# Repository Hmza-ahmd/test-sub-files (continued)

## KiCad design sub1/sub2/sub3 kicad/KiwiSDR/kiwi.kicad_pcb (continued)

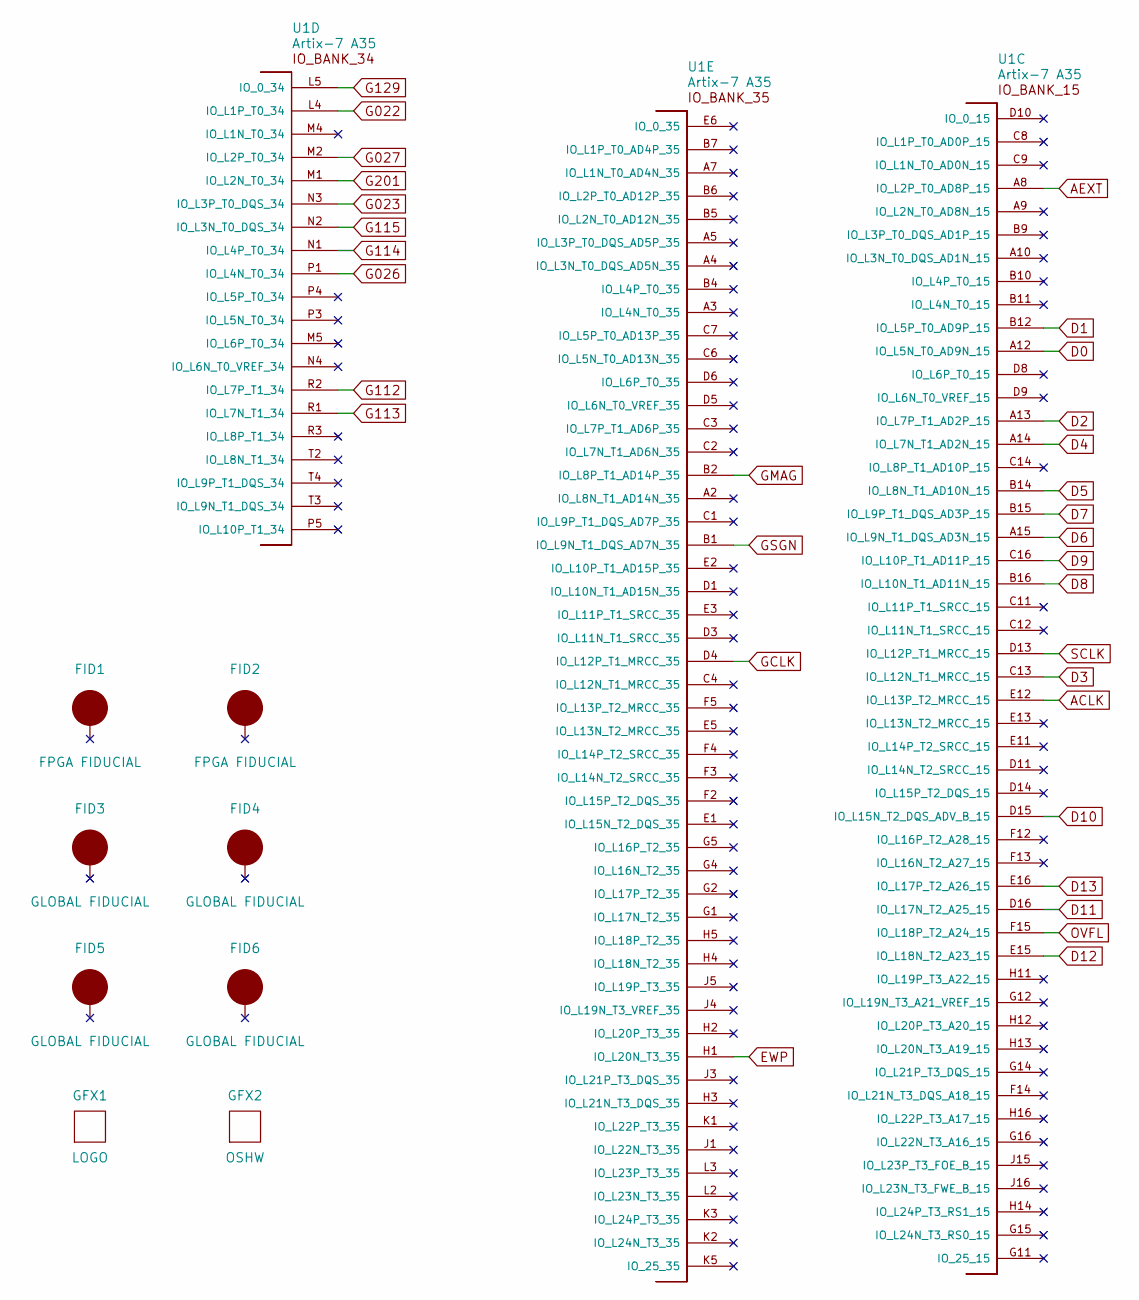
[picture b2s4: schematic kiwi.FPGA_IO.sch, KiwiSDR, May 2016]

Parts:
FID1, FID2: FPGA FIDUCIAL; kiwi-FIDUCIAL
FID3, FID4, FID5, FID6: GLOBAL FIDUCIAL; kiwi-FIDUCIAL
GFX1: LOGO; kiwi-KIWI_10MM
GFX2: OSHW; kiwi-OSHW_6MM
U1: Artix-7 A35; kiwi-FTG256

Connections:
ACLK: U1.E12 (IO_L13P_T2_MRCC_15); also elsewhere on the board
AEXT: U1.A8 (IO_L2P_T0_AD8P_15); also elsewhere on the board
D0: U1.A12 (IO_L5N_T0_AD9N_15); also elsewhere on the board
D1: U1.B12 (IO_L5P_T0_AD9P_15); also elsewhere on the board
D2: U1.A13 (IO_L7P_T1_AD2P_15); also elsewhere on the board
D3: U1.C13 (IO_L12N_T1_MRCC_15); also elsewhere on the board
D4: U1.A14 (IO_L7N_T1_AD2N_15); also elsewhere on the board
D5: U1.B14 (IO_L8N_T1_AD10N_15); also elsewhere on the board
D6: U1.A15 (IO_L9N_T1_DQS_AD3N_15); also elsewhere on the board
D7: U1.B15 (IO_L9P_T1_DQS_AD3P_15); also elsewhere on the board
D8: U1.B16 (IO_L10N_T1_AD11N_15); also elsewhere on the board
D9: U1.C16 (IO_L10P_T1_AD11P_15); also elsewhere on the board
D10: U1.D15 (IO_L15N_T2_DQS_ADV_B_15); also elsewhere on the board
D11: U1.D16 (IO_L17N_T2_A25_15); also elsewhere on the board
D12: U1.E15 (IO_L18N_T2_A23_15); also elsewhere on the board
D13: U1.E16 (IO_L17P_T2_A26_15); also elsewhere on the board
EWP: U1.H1 (IO_L20N_T3_35); also elsewhere on the board
G022: U1.L4 (IO_L1P_T0_34); also elsewhere on the board
G023: U1.N3 (IO_L3P_T0_DQS_34); also elsewhere on the board
G026: U1.P1 (IO_L4N_T0_34); also elsewhere on the board
G027: U1.M2 (IO_L2P_T0_34); also elsewhere on the board
G112: U1.R2 (IO_L7P_T1_34); also elsewhere on the board
G113: U1.R1 (IO_L7N_T1_34); also elsewhere on the board
G114: U1.N1 (IO_L4P_T0_34); also elsewhere on the board
G115: U1.N2 (IO_L3N_T0_DQS_34); also elsewhere on the board
G129: U1.L5 (IO_0_34); also elsewhere on the board
G201: U1.M1 (IO_L2N_T0_34); also elsewhere on the board
GCLK: U1.D4 (IO_L12P_T1_MRCC_35); also elsewhere on the board
GMAG: U1.B2 (IO_L8P_T1_AD14P_35); also elsewhere on the board
GSGN: U1.B1 (IO_L9N_T1_DQS_AD7N_35); also elsewhere on the board
OVFL: U1.F15 (IO_L18P_T2_A24_15); also elsewhere on the board
SCLK: U1.D13 (IO_L12P_T1_MRCC_15); also elsewhere on the board

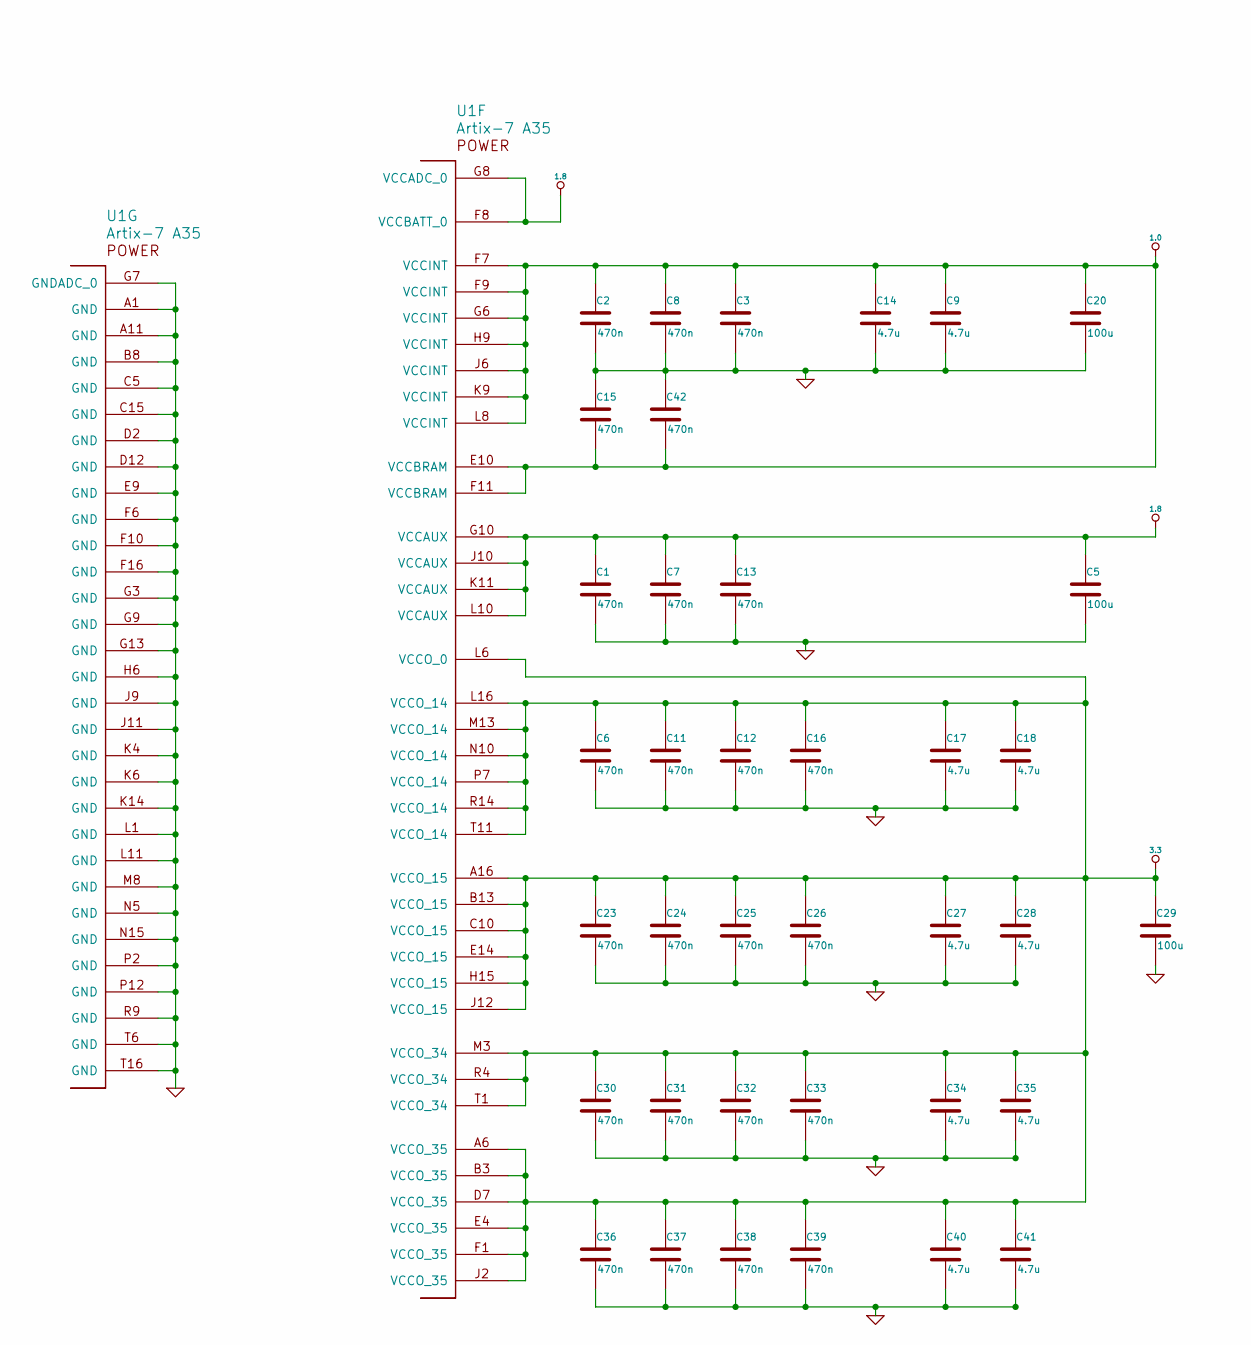
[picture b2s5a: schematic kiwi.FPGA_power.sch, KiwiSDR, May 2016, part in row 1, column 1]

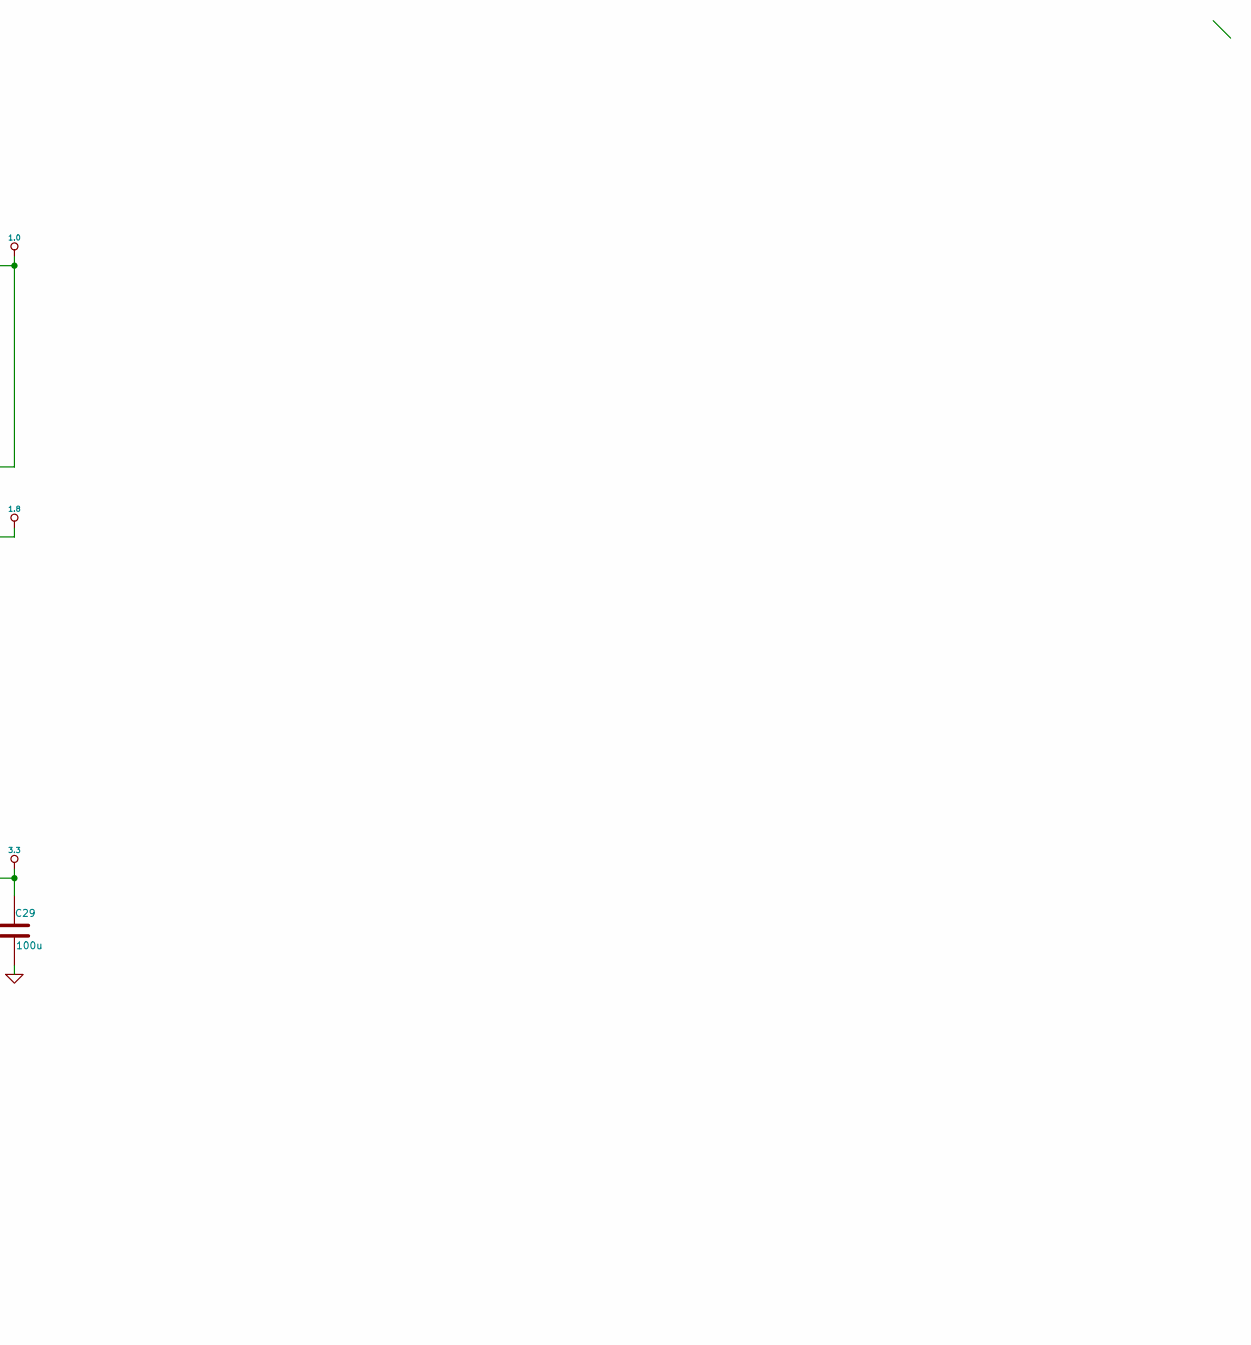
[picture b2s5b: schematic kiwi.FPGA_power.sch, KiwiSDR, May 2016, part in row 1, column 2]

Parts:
C1, C2, C3, C6, C7, C8, C11, C12, C13, C15, C16, C23, C24, C25, C26, C30, C31, C32, C33, C36, C37, C38, C39, C42: 470n; kiwi-SM0402
C5, C20, C29: 100u; kiwi-SM1206
C9, C14, C17, C18, C27, C28, C34, C35, C40, C41: 4.7u; kiwi-SM0402
U1: Artix-7 A35; kiwi-FTG256

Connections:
1.0: C2.1, C3.1, C8.1, C9.1, C14.1, C15.2, C20.1, C42.2, U1.E10 (VCCBRAM), U1.F7 (VCCINT), U1.F9 (VCCINT), U1.F11 (VCCBRAM), U1.G6 (VCCINT), U1.H9 (VCCINT), U1.J6 (VCCINT), U1.K9 (VCCINT), U1.L8 (VCCINT); also elsewhere on the board
1.8: C1.1, C5.1, C7.1, C13.1, U1.F8 (VCCBATT_0), U1.G8 (VCCADC_0), U1.G10 (VCCAUX), U1.J10 (VCCAUX), U1.K11 (VCCAUX), U1.L10 (VCCAUX); also elsewhere on the board

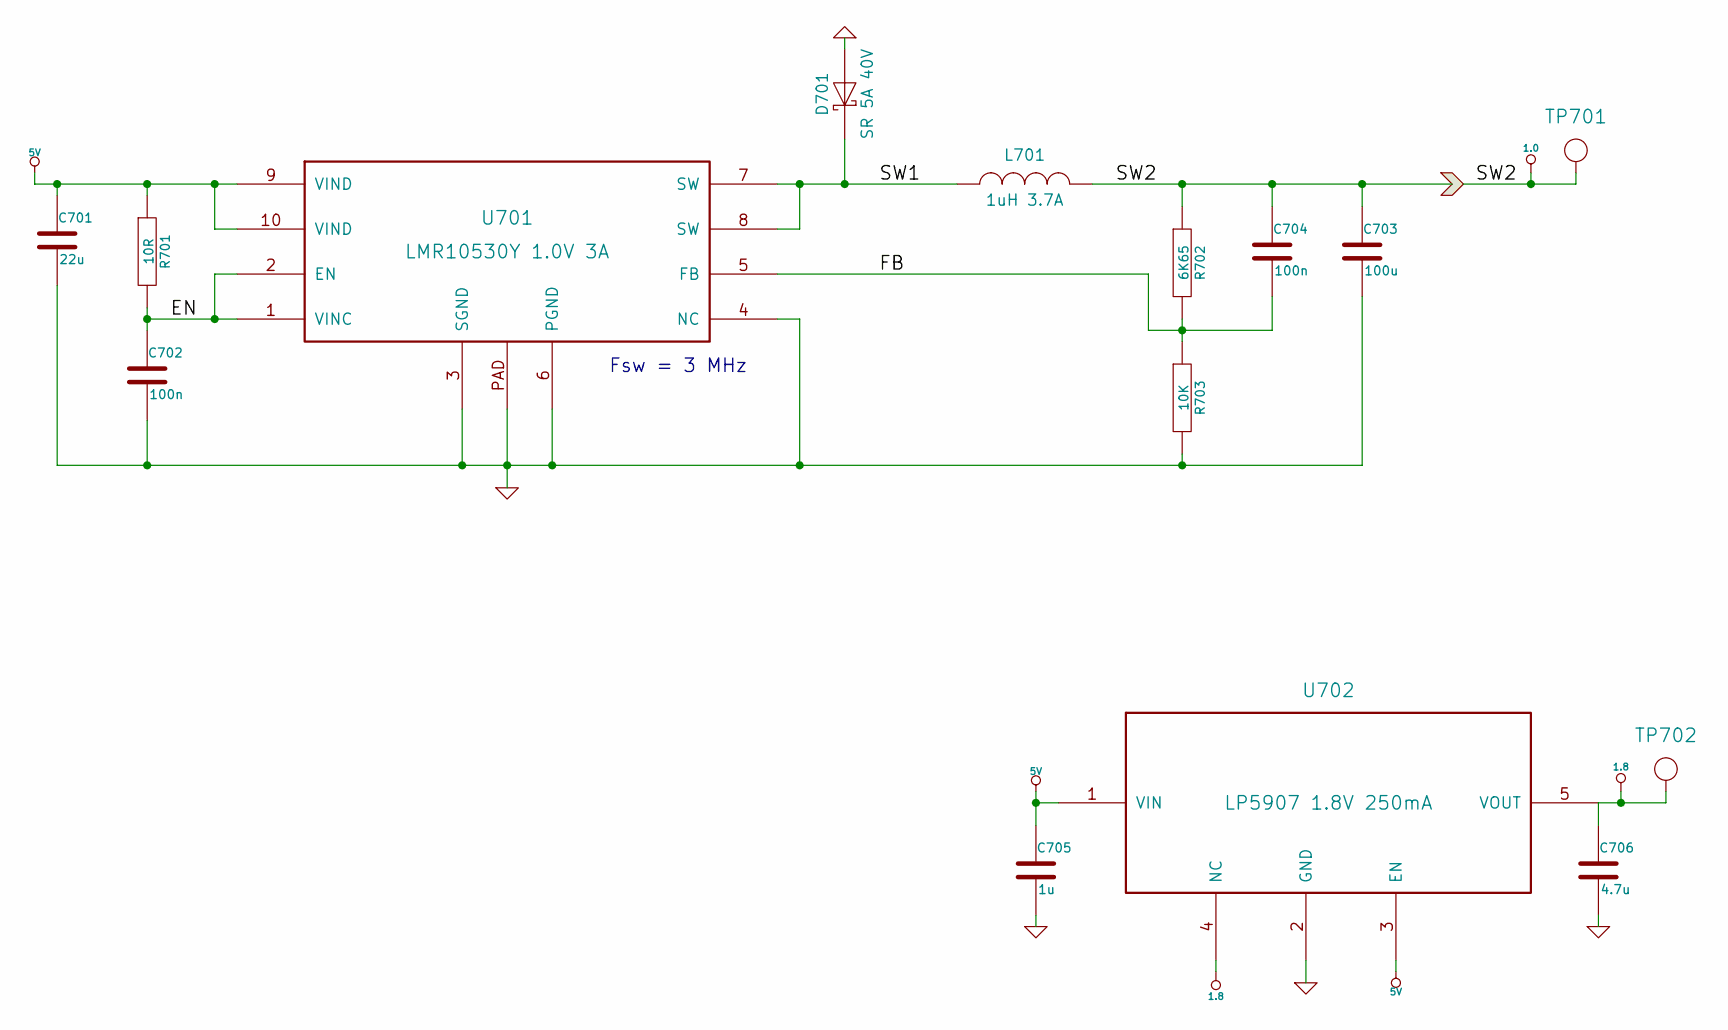
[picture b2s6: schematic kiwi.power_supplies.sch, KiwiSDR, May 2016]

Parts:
C701: 22u; kiwi-SM0805
C702, C704: 100n; kiwi-SM0402
C703: 100u; kiwi-SM1206
C705: 1u; kiwi-SM0402
C706: 4.7u; kiwi-SM0402
D701: SR 5A 40V; kiwi-DO214_AA
L701: 1uH 3.7A; kiwi-INDUCTOR_4x4
R701: 10R; kiwi-SM0402
R702: 6K65; kiwi-SM0402
R703: 10K; kiwi-SM0402
TP701, TP702: TEST_POINT; kiwi-TP_600
U701: LMR10530Y 1.0V 3A; kiwi-WSON10
U702: LP5907 1.8V 250mA; kiwi-SOT23_5

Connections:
1.0: C703.1, C704.1, L701.2, R702.1, TP701.1; also elsewhere on the board
1.8: C706.1, TP702.1, U702.4 (NC), U702.5 (VOUT); also elsewhere on the board
/Power_Supplies/EN: C702.1, R701.2, U701.1 (VINC), U701.2 (EN)
/Power_Supplies/FB: C704.2, R702.2, R703.1, U701.5 (FB)
/Power_Supplies/SW1: D701.1 (K), L701.1, U701.7 (SW), U701.8 (SW)

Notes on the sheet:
Fsw = 3 MHz

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
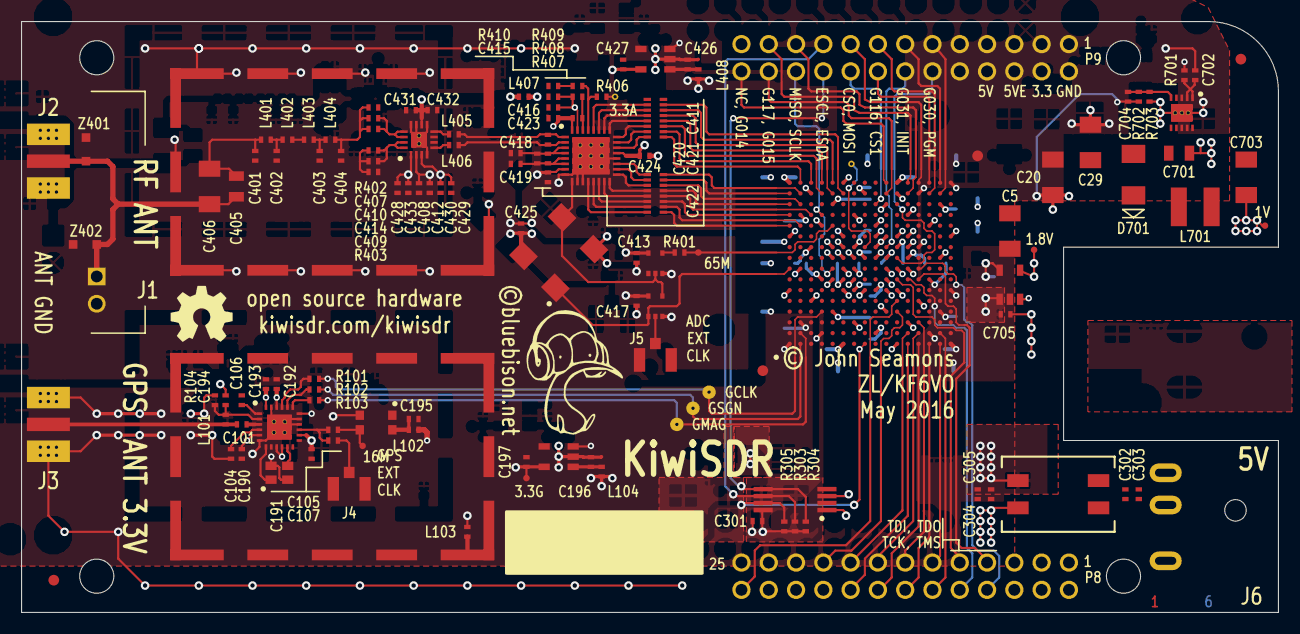
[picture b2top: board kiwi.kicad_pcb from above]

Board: 6 copper layers, 117.0 x 55.0 mm, 174 parts (0 on the bottom side), 119 nets.

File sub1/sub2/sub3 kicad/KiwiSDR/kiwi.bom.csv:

#1, 1, 0R, Panasonic, ERJ-2GE0R00X, kiwi-SM0402, R408
#2, 1, 10R, Panasonic, ERJ-2RKF10R0X, kiwi-SM0402, R701
#3, 1, 28R7, Panasonic, ERJ-2RKF28R7X, kiwi-SM0402, R403
#4, 1, 66R5, Panasonic, ERJ-2RKF66R5X, kiwi-SM0402, R402
#5, 4, 100R, Panasonic, ERJ-2RKF1000X, kiwi-SM0402, R101 R102 R103 R401
#6, 1, 1K5, Panasonic, ERJ-2RKF1501X, kiwi-SM0402, R104
#7, 3, 5K6, Panasonic, ERJ-2RKF5601X, kiwi-SM0402, R303 R304 R305
#8, 1, 6K65, Panasonic, ERJ-2RKF6651X, kiwi-SM0402, R702
#9, 4, 10K, Panasonic, ERJ-2RKF1002X, kiwi-SM0402, R406 R409 R410 R703
#10, 2, 100R, Bourns, CAY16-101J8LF, kiwi-RNET_CAY16_J8, R404 R405
#11, 2, 22p, Murata, GRM1555C1H220JA01D, kiwi-SM0402, C101 C104
#12, 2, 56p/100, Murata, GRM1555C2A560JA01D, kiwi-SM0402, C401 C404
#13, 4, 100p, Murata, GRM1555C1H101JA01D, kiwi-SM0402, C194 C408 C411 C416
#14, 2, 160p/50, Murata, GRM1555C1H161JA01D, kiwi-SM0402, C402 C403
#15, 5, 1n, Murata, GCM155R71H102KA37D, kiwi-SM0402, C407 C409 C428 C430 C432
#16, 8, 10n, Murata, GRM155R71C103KA01D, kiwi-SM0402, C105 C106 C193 C303 C305 C413 C417 C425
#17, 14, 100n, Murata, GRM155R71C104KA88D, kiwi-SM0402, C190 C191 C192 C195 C301 C421 C422 C423 C424 C429 C431 C433 C702 C704
#18, 28, 470n, Murata, GRM155R6YA474KE01D, kiwi-SM0402, C1 C2 C3 C6 C7 C8 C11 C12 C13 C15 C16 C23 C24 C25 C26 C30 C31 C32 C33 C36 C37 C38 C39 C42 C302 C304 C410 C414
#19, 7, 1u, Murata, GRM155R61E105KA12D, kiwi-SM0402, C196 C197 C418 C419 C426 C427 C705
#20, 3, 2.2u, Murata, GRM155R60J225ME15D, kiwi-SM0402, C412 C415 C420
#21, 11, 4.7u, Murata, GRM155R60J475ME47D, kiwi-SM0402, C9 C14 C17 C18 C27 C28 C34 C35 C40 C41 C706
#22, 1, 1n/100, Murata, GRM219R72A102KA01J, kiwi-SM0805, C405
#23, 1, 22u, Murata, GRM21BR60J226ME39L, kiwi-SM0805, C701
#24, 1, 470n/100, AVX, ESD61C474K4T2A-28, kiwi-SM1206, C406
#25, 4, 100u, Murata, GRM31CR60J107ME39L, kiwi-SM1206, C5 C20 C29 C703
#26, 5, FB 600Z, TDK, MMZ1005B601C, kiwi-SM0402, L102 L103 L104 L407 L408
#27, 1, 39nH, TDK, MLK1005S39NJ, kiwi-SM0402, L101
#28, 3, 150nH, TDK, MLG1005SR15J, kiwi-SM0402, L403 L405 L406
#29, 1, 270nH, TDK, MLG1005SR27J, kiwi-SM0402, L402
#30, 2, 330nH, TDK, MLG1005SR33J, kiwi-SM0402, L401 L404
#31, 1, 1uH 3.7A, Bourns, SRN4018-1R0Y, kiwi-INDUCTOR_4x4, L701
#32, 1, CMC 500uH 1A, Bourns, SRF0905A-501Y, kiwi-CMC, T301
#33, 1, SAW L1, RFM, SF1186G, kiwi-SAW, FL101
#34, 1, SE4150L, Skyworks, SE4150L-R, kiwi-QFN24, U101
#35, 1, EEPROM 32Kx8, On Semi, CAT24C256YI-GT3, kiwi-TSSOP8, U301
#36, 2, NC7SZ125, Fairchild, NC7SZ125P5X, kiwi-SC70_5, U403 U406
#37, 1, LMR10530Y 1.0V 3A, TI, LMR10530YSD/NOPB, kiwi-WSON10, U701
#38, 2, LP5907 3.3V 250mA, TI, LP5907QMFX-3.3Q1, kiwi-SOT23_5, U104 U404
#39, 1, LP5907 1.8V 250mA, TI, LP5907QMFX-1.8Q1, kiwi-SOT23_5, U702
#40, 1, SR 5A 40V, Vishay, SSB44-E3/52T, kiwi-DO214_AA, D701
#41, 2, TVS 3.3V, Bourns, CDSOD323-T03C, kiwi-SOD323, Z401 Z402
#42, 1, 66.6666 MHz, Conner Winfield, CWX823-066.6666M, kiwi-XO, U402
#43, 1, 16.368 MHz, TXC, 7Q-16.368MBG-T, kiwi-TCXO, X101
#44, 2, RF_SHIELD 29x19, Laird, BMI-S-209-F, *, ZR401 ZR101
#45, 2, RF_SHIELD_COVER 29x19, Laird, BMI-S-209-C, kiwi-RF_SHIELD_COVER, ZR102 ZR402
#46, 1, Artix-7 A35, Xilinx, XC7A35T-1FTG256C, kiwi-FTG256, U1
#47, 1, LTC2248, Linear Tech, LTC2248CUH#PBF, kiwi-QFN32, U401
#48, 1, LTC6401-20, Linear Tech, LTC6401CUD-20#PBF, kiwi-QFN16, U405

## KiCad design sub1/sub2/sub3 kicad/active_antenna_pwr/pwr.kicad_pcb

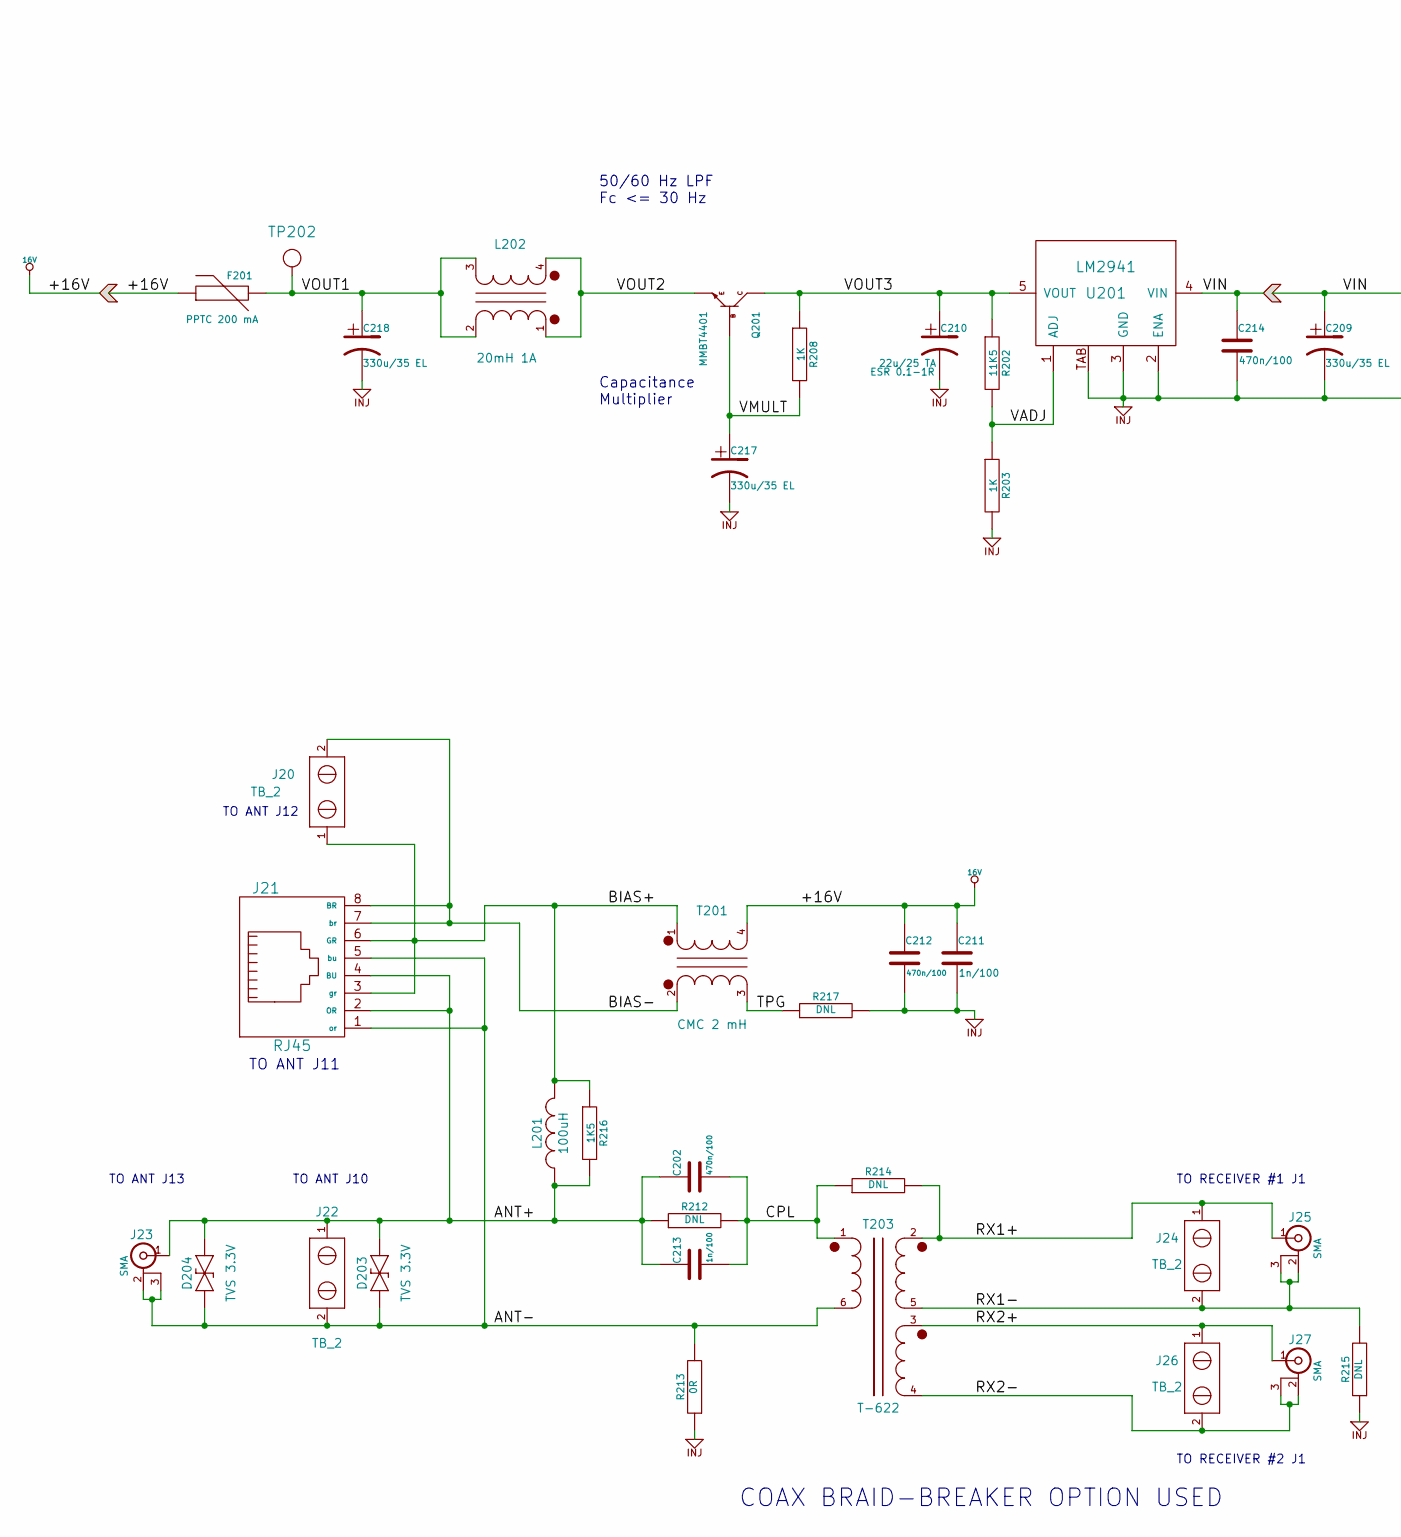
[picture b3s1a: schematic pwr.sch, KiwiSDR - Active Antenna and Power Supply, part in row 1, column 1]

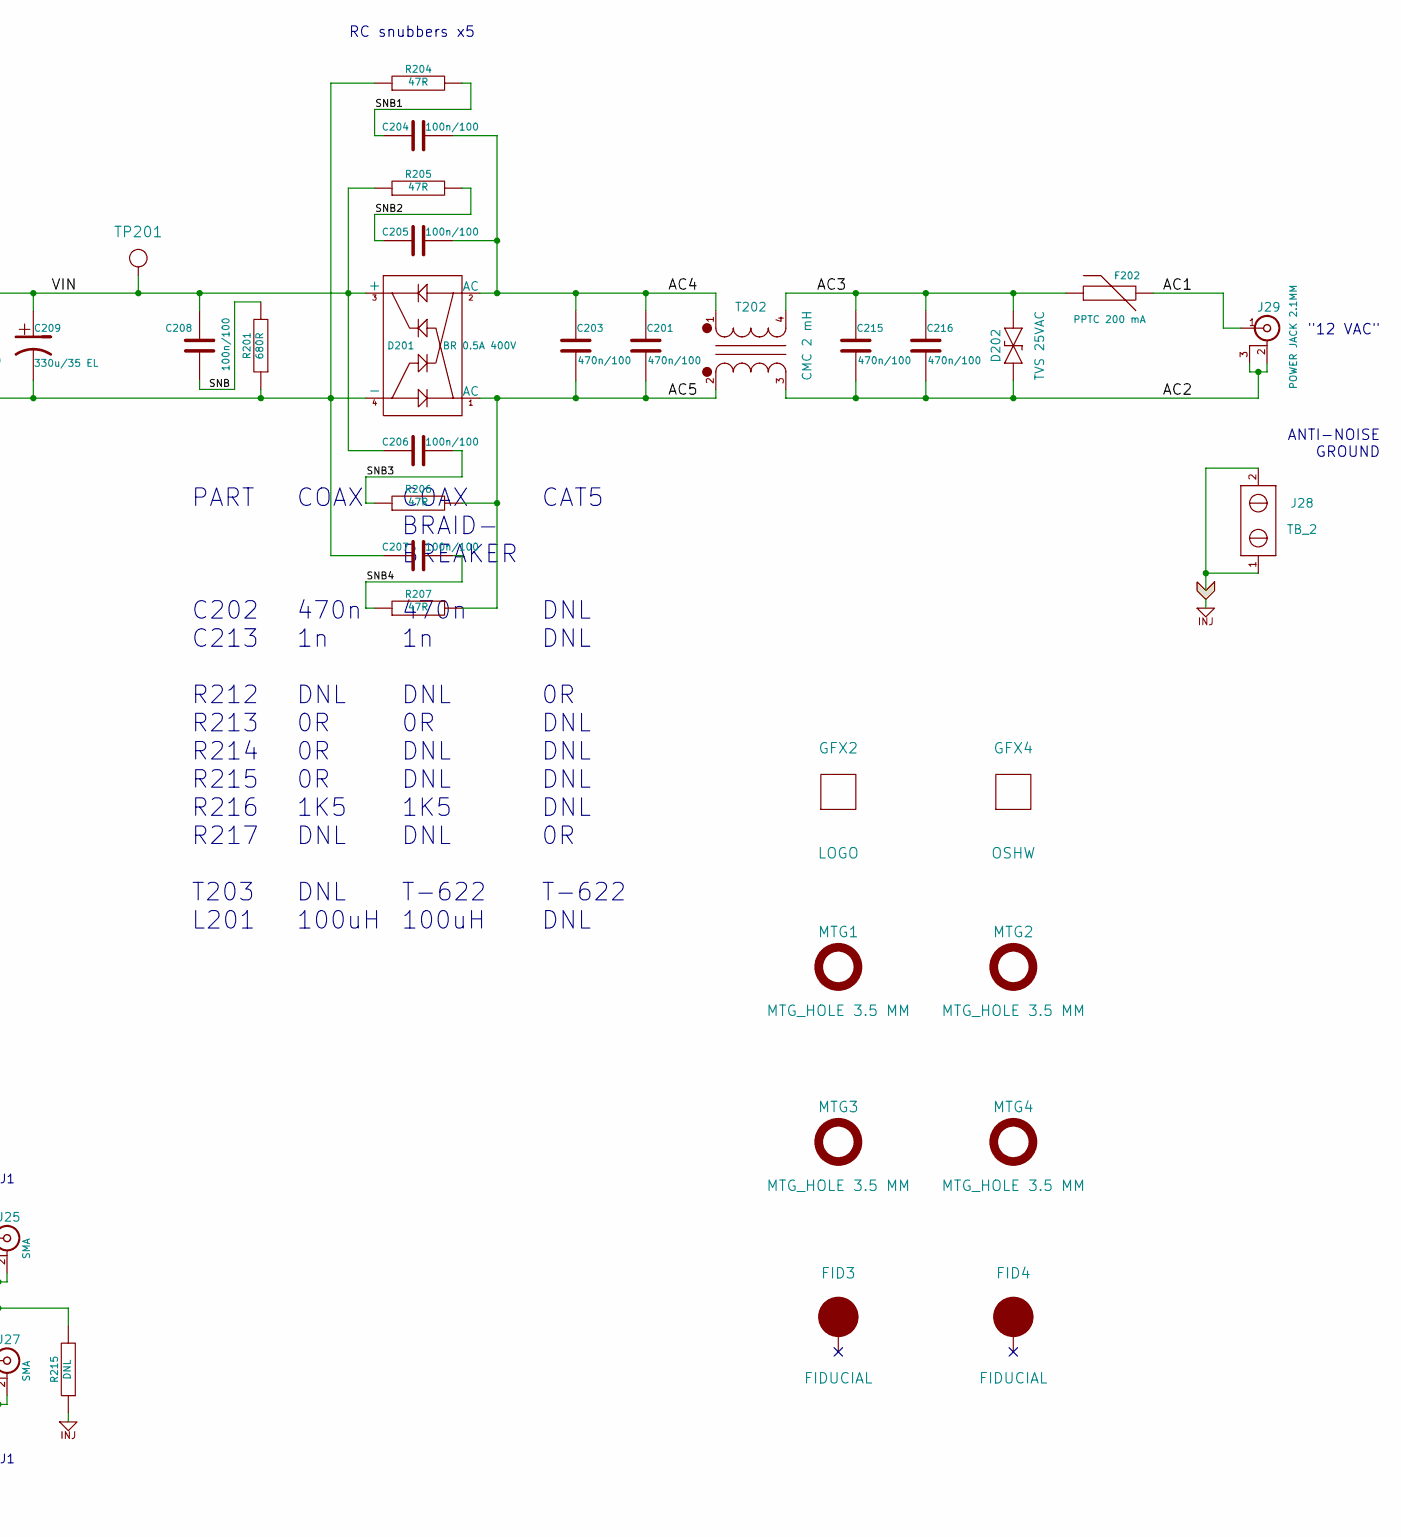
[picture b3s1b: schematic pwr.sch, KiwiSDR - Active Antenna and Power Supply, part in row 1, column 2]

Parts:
C201, C202, C203, C212, C214, C215, C216: 470n/100; kiwi-SM1206
C204, C205, C206, C207, C208: 100n/100; kiwi-SM0805
C209, C217, C218: 330u/35 EL; kiwi-CAP_10x10
C210: 22u/25 TA; kiwi-CAP_D
C211, C213: 1n/100; kiwi-SM0805
D201: BR 0.5A 400V; kiwi-TO269_AA
D202: TVS 25VAC; kiwi-SM0805
D203, D204: TVS 3.3V; kiwi-SOD323
F201, F202: PPTC 200 mA; kiwi-SM1812
FID3, FID4: FIDUCIAL; kiwi-FIDUCIAL
GFX2: LOGO; kiwi-KIWI_10MM
GFX4: OSHW; kiwi-OSHW_6MM
J20, J22, J24, J26, J28: TB_2; kiwi-TB_2P_2_54MM
J21: RJ45; kiwi-RJ45_8
J23, J25, J27: SMA; kiwi-BNC_SMA_NO_VIP
J29: POWER JACK 2.1MM; kiwi-DC_JACK_2_1MM
L201: 100uH; kiwi-SM1812
L202: 20mH 1A; kiwi-CMC_22x22
MTG1, MTG2, MTG3, MTG4: MTG_HOLE 3.5 MM; kiwi-MTG_NPTH_3_5MM
Q201: MMBT4401; kiwi-SOT23_BCE
R201: 680R; kiwi-SM0805
R202: 11K5; kiwi-SM0805
R203, R208: 1K; kiwi-SM0805
R204, R205, R206, R207: 47R; kiwi-SM0805
R212, R214, R215, R217: DNL; kiwi-SM0805
R213: 0R; kiwi-SM0805
R216: 1K5; kiwi-SM0805
T201, T202: CMC 2 mH; kiwi-CMC
T203: T-622; kiwi-MCL_KK81
TP201, TP202: TEST_POINT; kiwi-TP_1250
U201: LM2941; kiwi-TO263

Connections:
/AC1: F202.2, J29.1 (In)
/AC2: C215.2, C216.2, D202.1, J29.2 (gnd), J29.3 (gnd), T202.3
/AC3: C215.1, C216.1, D202.2, F202.1, T202.4
/AC4: C201.1, C203.1, C204.2, C205.2, D201.2 (AC), T202.1
/AC5: C201.2, C203.2, D201.1 (AC), R206.2, R207.2, T202.2
/ANT+: C202.1, C213.1, D203.2, D204.2, J21.2 (OR), J21.4 (BU), J22.1, J23.1 (In), L201.1, R212.1, R216.2
/ANT-: D203.1, D204.1, J21.1 (or), J21.5 (bu), J22.2, J23.2 (gnd), J23.3 (gnd), R213.2, T203.6
/BIAS+: J20.1, J21.3 (gr), J21.6 (GR), L201.2, R216.1, T201.1
/BIAS-: J20.2, J21.7 (br), J21.8 (BR), T201.2
/CPL: C202.2, C213.2, R212.2, R214.1, T203.1
/RX1+: J24.1, J25.1 (In), R214.2, T203.2
/RX1-: J24.2, J25.2 (gnd), J25.3 (gnd), R215.2, T203.5
/RX2+: J26.1, J27.1 (In), T203.3
/RX2-: J26.2, J27.2 (gnd), J27.3 (gnd), T203.4
/SNB: C208.2, R201.2
/SNB1: C204.1, R204.2
/SNB2: C205.1, R205.2
/SNB3: C206.2, R206.1
/SNB4: C207.2, R207.1
/TPG: R217.1, T201.3
/VADJ: R202.2, R203.1, U201.1 (ADJ)
/VMULT: C217.1, Q201.B, R208.2
/VOUT1: C218.1, F201.2, L202.2, L202.3, TP202.1
/VOUT2: L202.1, L202.4, Q201.E
/VOUT3: C210.1, Q201.C, R202.1, R208.1, U201.5 (VOUT)

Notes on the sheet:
"12 VAC"
RC snubbers x5
PART C202 C213 R212 R213 R214 R215 R216 R217 T203 L201
COAX BRAID- BREAKER 470n 1n DNL 0R DNL DNL 1K5 DNL T-622 100uH
CAT5 DNL DNL 0R DNL DNL DNL DNL 0R T-622 DNL
TO ANT J12
TO ANT J11
TO RECEIVER #1 J1
TO ANT J10
50/60 Hz LPF Fc <= 30 Hz
Capacitance Multiplier
ANTI-NOISE GROUND
COAX 470n 1n DNL 0R 0R 0R 1K5 DNL DNL 100uH
TO ANT J13
TO RECEIVER #2 J1
COAX BRAID-BREAKER OPTION USED

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
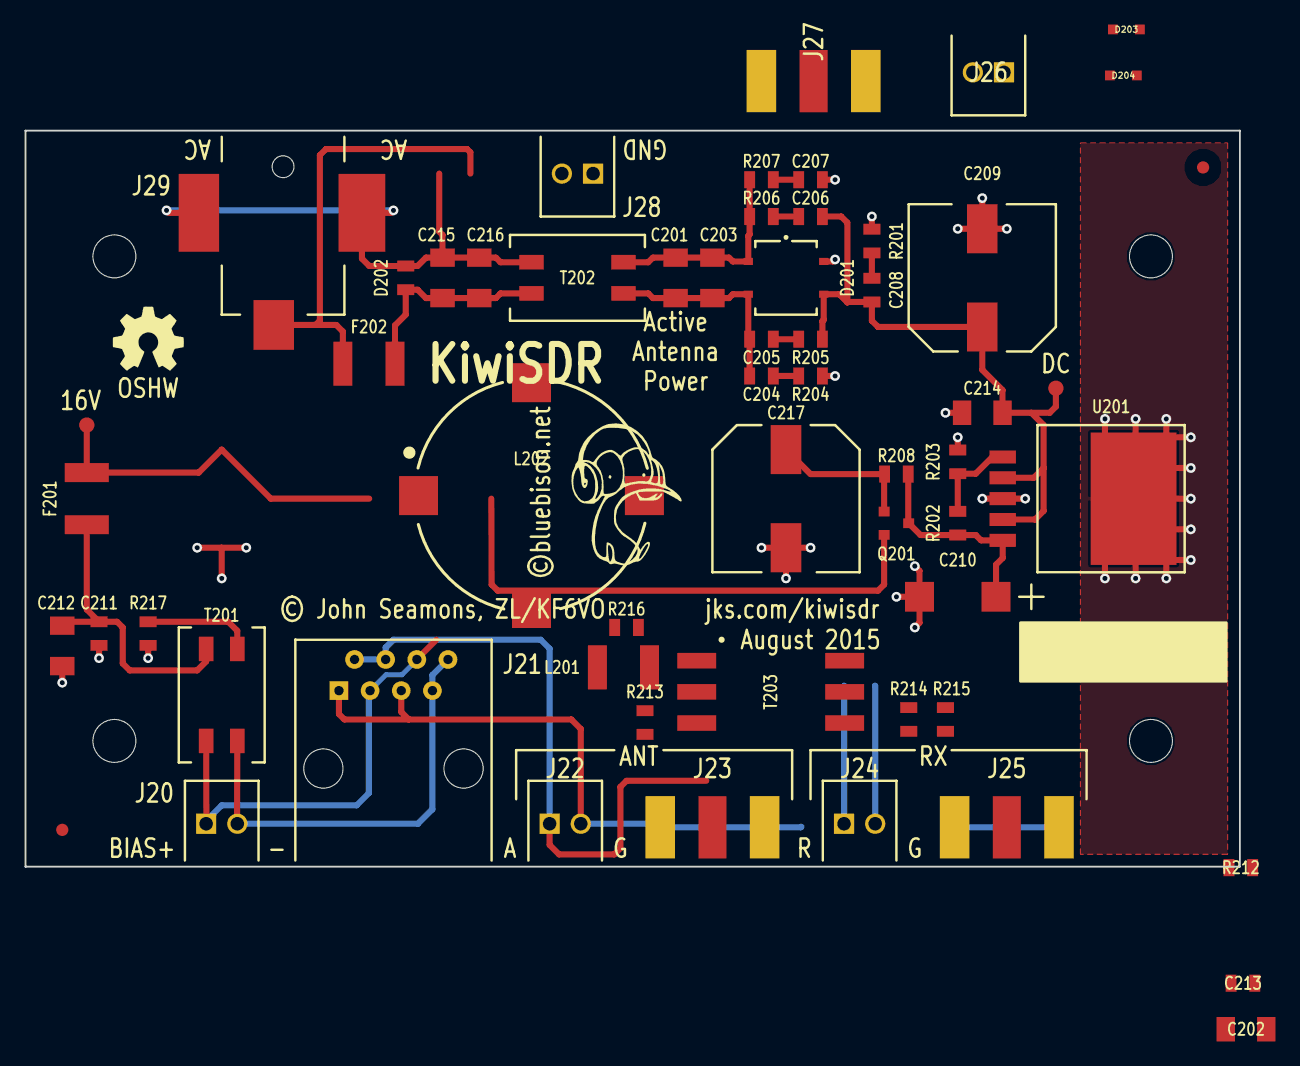
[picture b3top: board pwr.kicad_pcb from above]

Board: 2 copper layers, 99.0 x 60.0 mm, 64 parts (0 on the bottom side), 29 nets.

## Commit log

2021-01-14 1st commit
